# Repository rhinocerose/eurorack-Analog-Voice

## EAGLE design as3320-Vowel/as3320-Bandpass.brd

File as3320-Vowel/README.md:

# 3320 BPF

In Design

CC-BY-NC-SA 4.0

Based on :

https://github.com/forestcaver/Analog-Voice/tree/master/AJH_as3320_LPF

By  Forest Caver

Formant Information :
http://www.u.arizona.edu/~ohalad/Phonetics/notes/Formants%20Spectrograms%20and%20Vowels.PDF

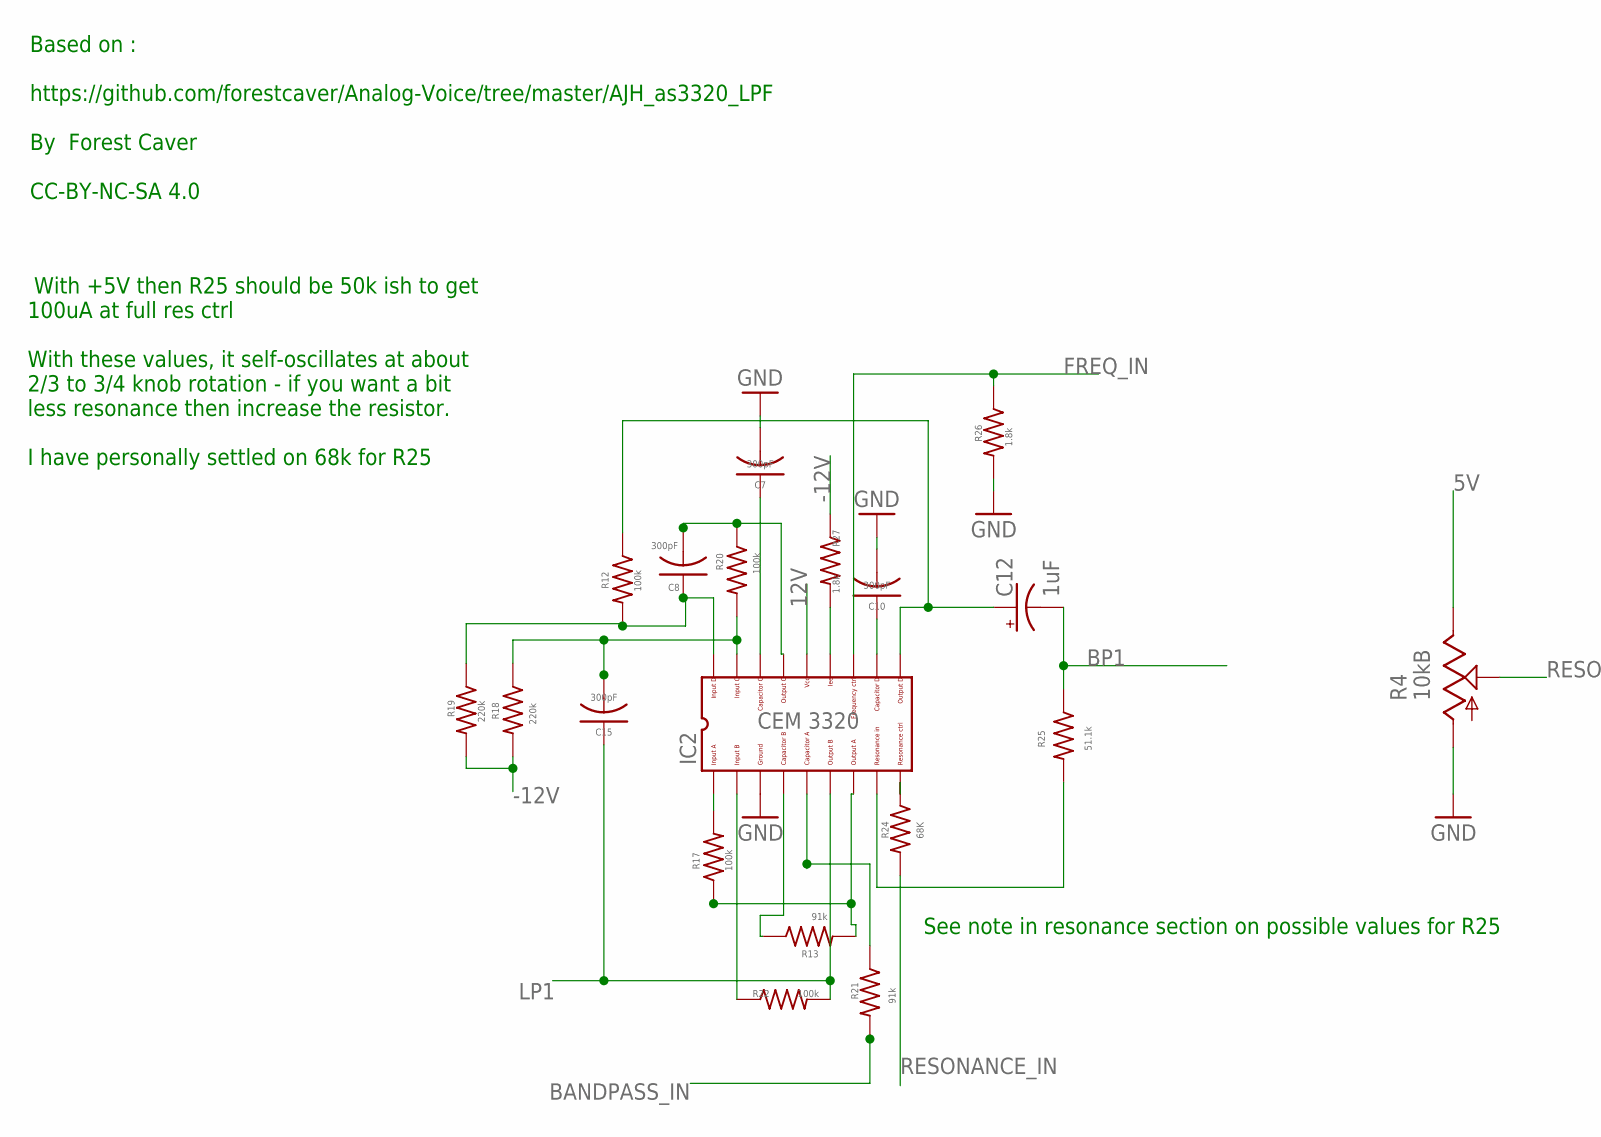
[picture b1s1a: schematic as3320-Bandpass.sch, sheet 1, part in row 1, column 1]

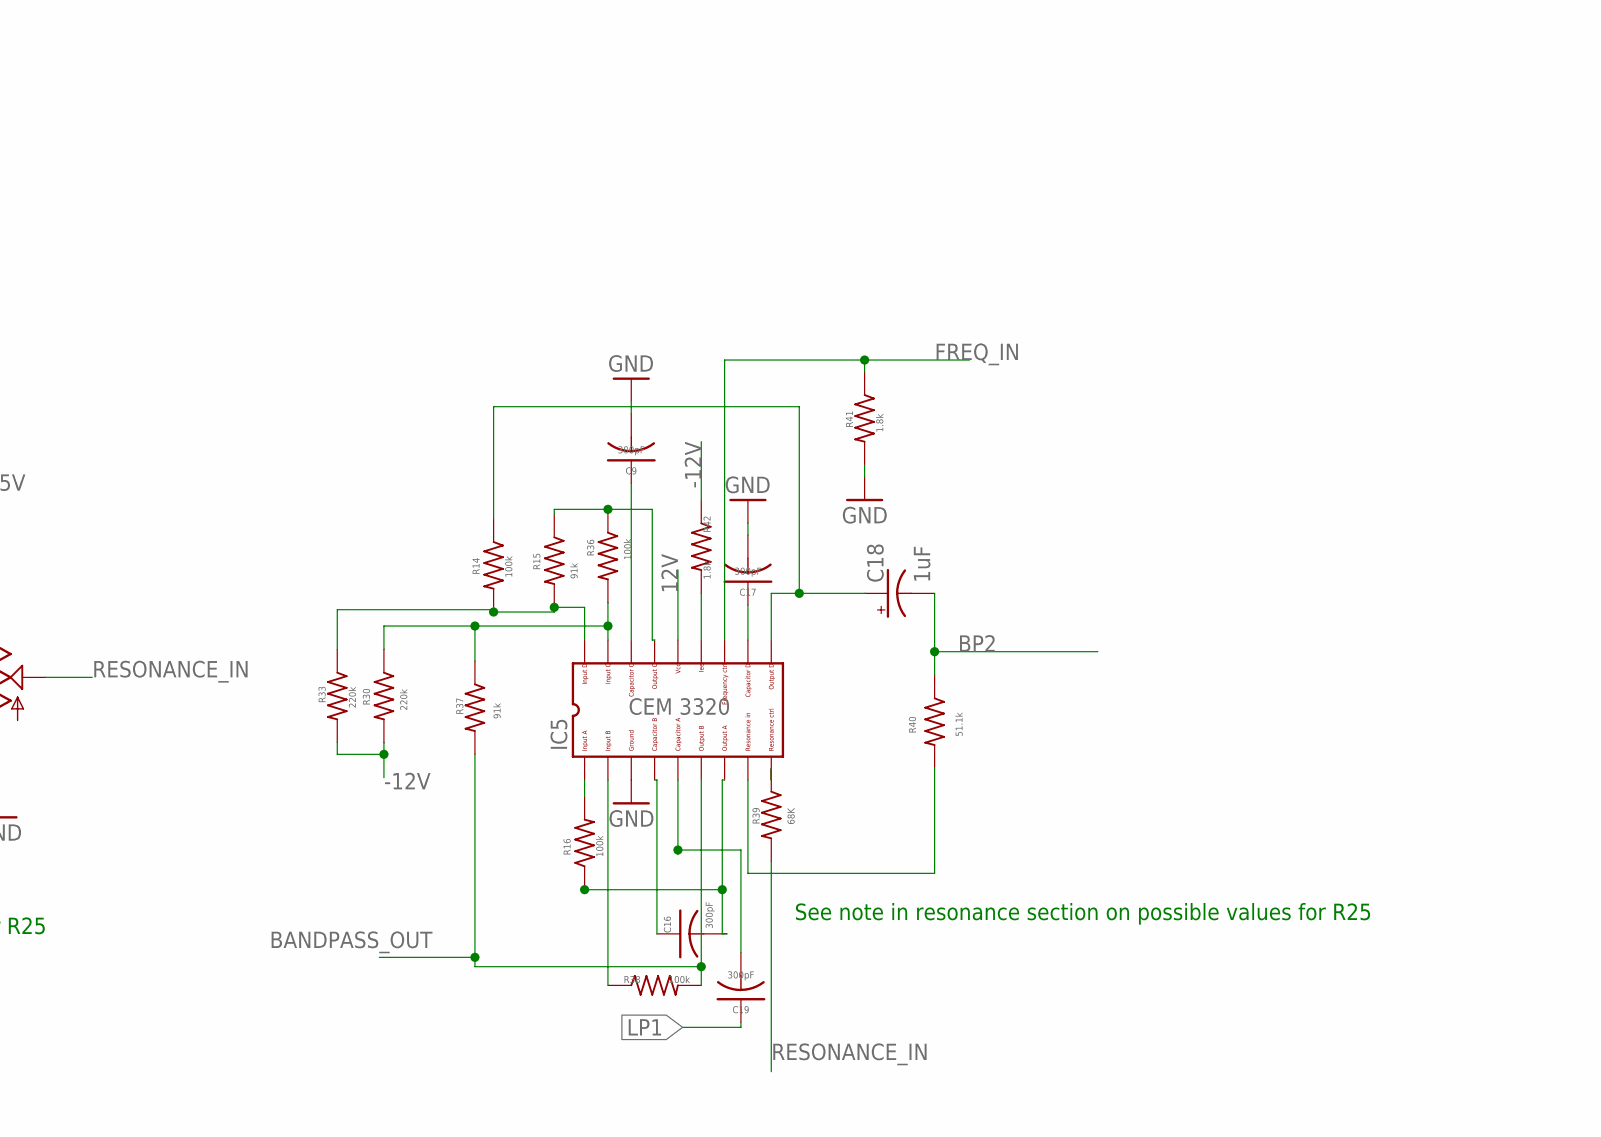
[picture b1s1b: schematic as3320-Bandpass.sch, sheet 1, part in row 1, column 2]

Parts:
C7, C8, C9, C10, C15, C16, C17, C19: 300pF; C0603
C12, C18: 1uF; PANASONIC_B
IC2, IC5: CEM3320; DIL18
R4: 10kB; ALPS_POT_VERTICAL
R12, R14, R16, R17, R20, R22, R36, R38: 100k; R0603
R13, R15, R21, R37: 91k; R0603
R18, R19, R30, R33: 220k; R0603
R24, R39: 68K; R0603
R25, R40: 51.1k; R0603
R26, R27, R41, R42: 1.8k; R0603

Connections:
5V: R4.P$1 (E); also elsewhere on the board
12V: IC2.14, IC5.14; also elsewhere on the board
-12V: R18.2, R19.2, R27.1, R30.2, R33.2, R42.1; also elsewhere on the board
BANDPASS_IN: R21.2; also elsewhere on the board
BANDPASS_OUT: IC5.6, R37.2, R38.2; also elsewhere on the board
BP1: C12.-, R25.1
BP2: C18.-, R40.1
FREQ_IN: IC2.12, IC5.12, R26.1, R41.1; also elsewhere on the board
GND: C7.2, C9.2, C10.2, C17.2, IC2.3, IC5.3, R4.P$3 (A), R26.2, R41.2; also elsewhere on the board
LP1: C15.1, C19.1, IC2.6, R22.2
unnamed: C10.1, IC2.11
unnamed: IC2.9, R24.1
unnamed: IC2.8, R25.2
unnamed: IC2.13, R27.2
unnamed: C17.1, IC5.11
unnamed: C7.1, IC2.16
unnamed: IC5.9, R39.1
unnamed: C12.+, IC2.10, R12.1
unnamed: IC2.5, R21.1
unnamed: IC2.7, R13.2, R17.1
unnamed: IC2.4, R13.1
unnamed: IC2.2, R22.1
unnamed: IC5.8, R40.2
unnamed: IC5.13, R42.2
unnamed: C9.1, IC5.16
unnamed: C18.+, IC5.10, R14.1
unnamed: C19.2, IC5.5
unnamed: C16.2, IC5.7, R16.1
unnamed: C16.1, IC5.4
unnamed: IC5.2, R38.1
unnamed: IC5.1, R16.2
unnamed: IC5.17, R30.1, R36.2, R37.1
unnamed: IC5.15, R15.1, R36.1
unnamed: IC5.18, R14.2, R15.2, R33.1
unnamed: IC2.1, R17.2
unnamed: C15.2, IC2.17, R18.1, R20.2
unnamed: C8.2, IC2.15, R20.1
unnamed: C8.1, IC2.18, R12.2, R19.1
RESONANCE_IN: R4.P$2 (S), R24.2, R39.2

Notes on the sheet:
With +5V then R25 should be 50k ish to get 100uA at full res ctrl With these values, it self-oscillates at about 2/3 to 3/4 knob rotation - if you want a bit less resonance then increase the resistor. I have personally settled on 68k for R25
Based on : https://github.com/forestcaver/Analog-Voice/tree/master/AJH_as3320_LPF By Forest Caver CC-BY-NC-SA 4.0
See note in resonance section on possible values for R25

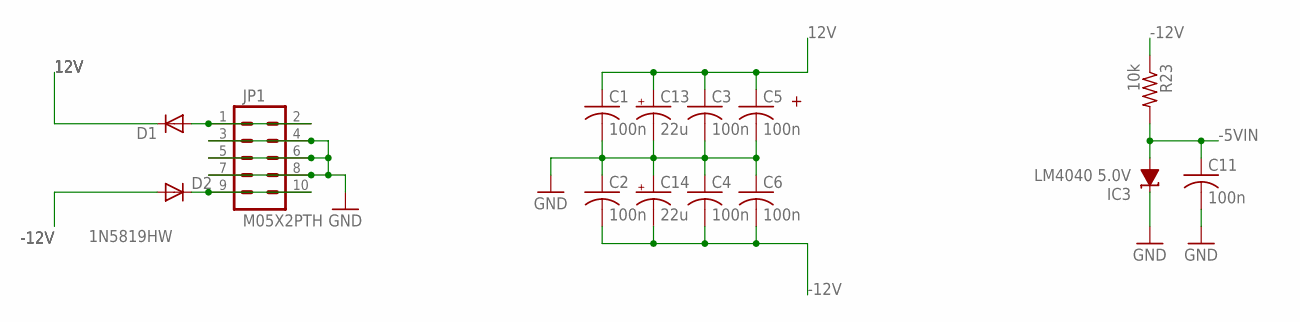
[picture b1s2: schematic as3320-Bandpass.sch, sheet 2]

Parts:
C1, C2, C3, C4, C5, C6, C11: 100n; C0603
C13, C14: 22u; PANASONIC_B
D1, D2: 1N5819HW; SOD123
IC3: LM4040 5.0V; DBZ_R-PDSO-G3
JP1: M05X2PTH; AVR_ICSP
R23: 10k; R0603

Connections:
12V: C1.1, C3.1, C5.1, C13.+, D1.C; also elsewhere on the board
-5VIN: C11.1, IC3.2 (A), R23.2; also elsewhere on the board
-12V: C2.2, C4.2, C6.2, C14.-, D2.A, R23.1; also elsewhere on the board
GND: C1.2, C2.1, C3.2, C4.1, C5.2, C6.1, C11.2, C13.-, C14.+, IC3.1 (C), JP1.3, JP1.4, JP1.5, JP1.6, JP1.7, JP1.8; also elsewhere on the board
unnamed: D1.A, JP1.1, JP1.2
unnamed: D2.C, JP1.9, JP1.10

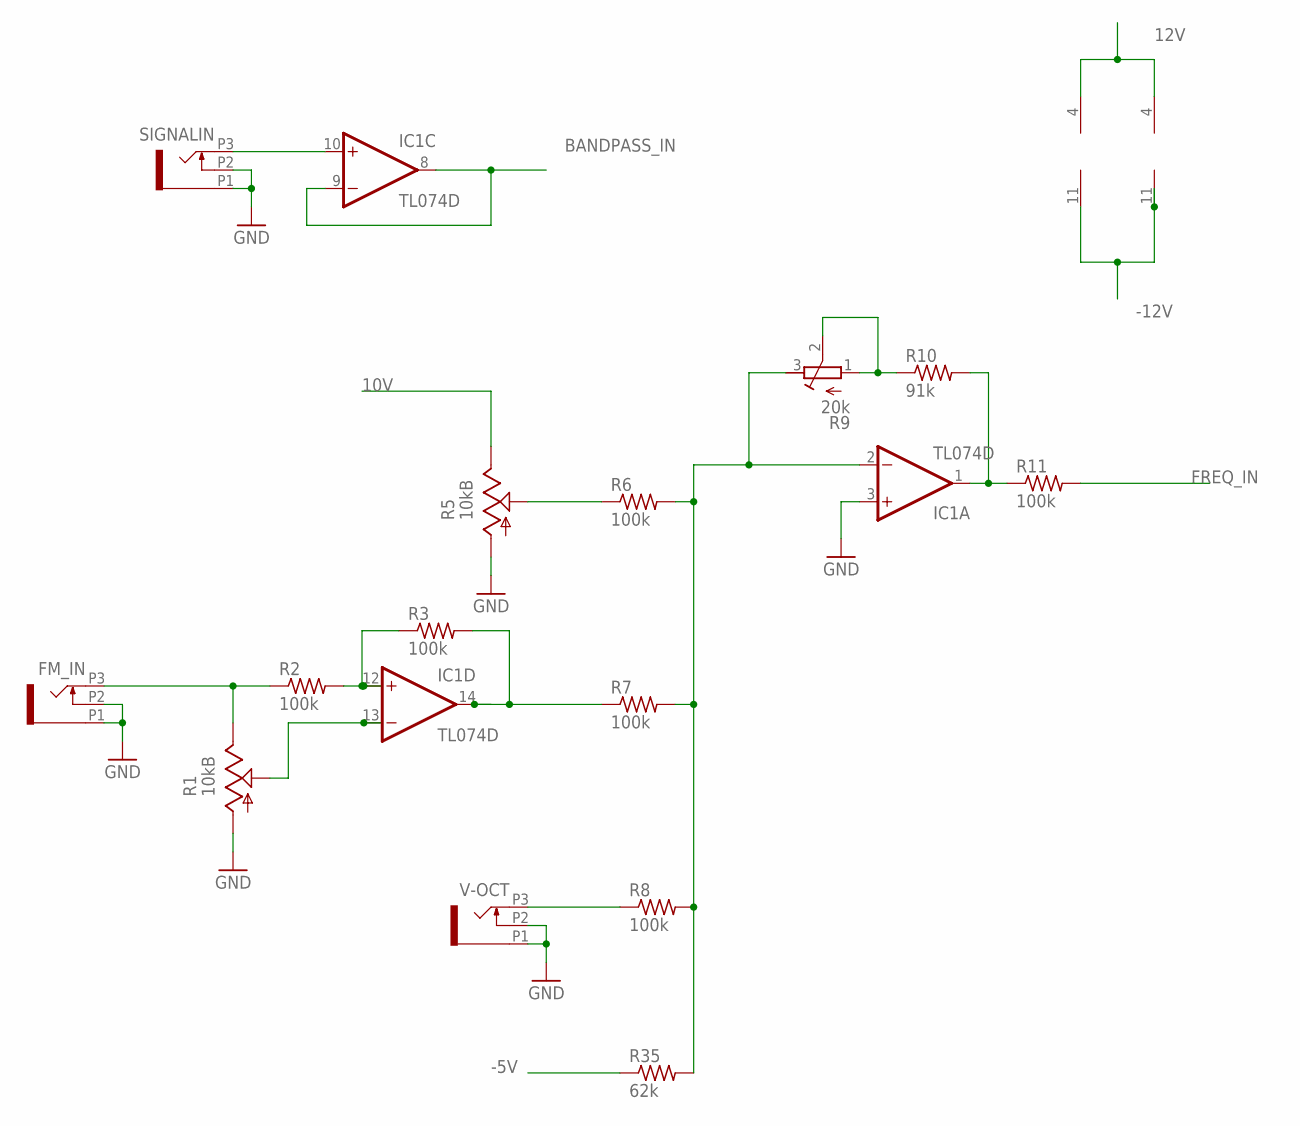
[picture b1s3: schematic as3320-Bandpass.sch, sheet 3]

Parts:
FM_IN: PJ301_THONKICONN6; WQP_PJ_301M6
IC1, IC4: TL074D; SO14
R1, R5: 10kB; ALPS_POT_VERTICAL
R2, R3, R6, R7, R8, R11: 100k; R0603
R9: 20k; RTRIM3296X
R10: 91k; R0603
R35: 62k; R0603
SIGNALIN: PJ301_THONKICONN6; WQP_PJ_301M6
V-OCT: PJ301_THONKICONN6; WQP_PJ_301M6

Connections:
10V: R5.P$1 (E); also elsewhere on the board
12V: IC1.4 (V+), IC4.4 (V+); also elsewhere on the board
-5V: R35.1; also elsewhere on the board
-12V: IC1.11 (V-), IC4.11 (V-); also elsewhere on the board
BANDPASS_IN: IC1.8 (OUT), IC1.9 (-IN); also elsewhere on the board
FREQ_IN: R11.2; also elsewhere on the board
GND: FM_IN.P1 (1), FM_IN.P2 (2), IC1.3 (+IN), R1.P$3 (A), R5.P$3 (A), SIGNALIN.P1 (1), SIGNALIN.P2 (2), V-OCT.P1 (1), V-OCT.P2 (2); also elsewhere on the board
unnamed: IC1.13 (-IN), R1.P$2 (S)
unnamed: R5.P$2 (S), R6.1
unnamed: IC1.12 (+IN), R2.2, R3.1
unnamed: IC1.2 (-IN), R6.2, R7.2, R8.2, R9.3 (A), R35.2
unnamed: IC1.1 (OUT), R10.2, R11.1
unnamed: IC1.10 (+IN), SIGNALIN.P3 (3)
unnamed: R8.1, V-OCT.P3 (3)
unnamed: IC1.14 (OUT), R3.2, R7.1
unnamed: R9.1 (E), R9.2 (S), R10.1
unnamed: FM_IN.P3 (3), R1.P$1 (E), R2.1

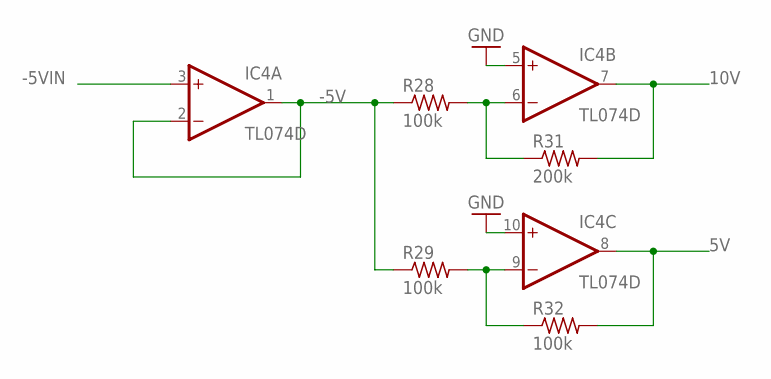
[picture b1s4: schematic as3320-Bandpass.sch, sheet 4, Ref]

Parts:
IC4: TL074D; SO14
R28, R29, R32: 100k; R0603
R31: 200k; R0603

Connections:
5V: IC4.8 (OUT), R32.2; also elsewhere on the board
10V: IC4.7 (OUT), R31.2; also elsewhere on the board
-5V: IC4.1 (OUT), IC4.2 (-IN), R28.1, R29.1; also elsewhere on the board
-5VIN: IC4.3 (+IN); also elsewhere on the board
GND: IC4.5 (+IN), IC4.10 (+IN); also elsewhere on the board
unnamed: IC4.9 (-IN), R29.2, R32.1
unnamed: IC4.6 (-IN), R28.2, R31.1

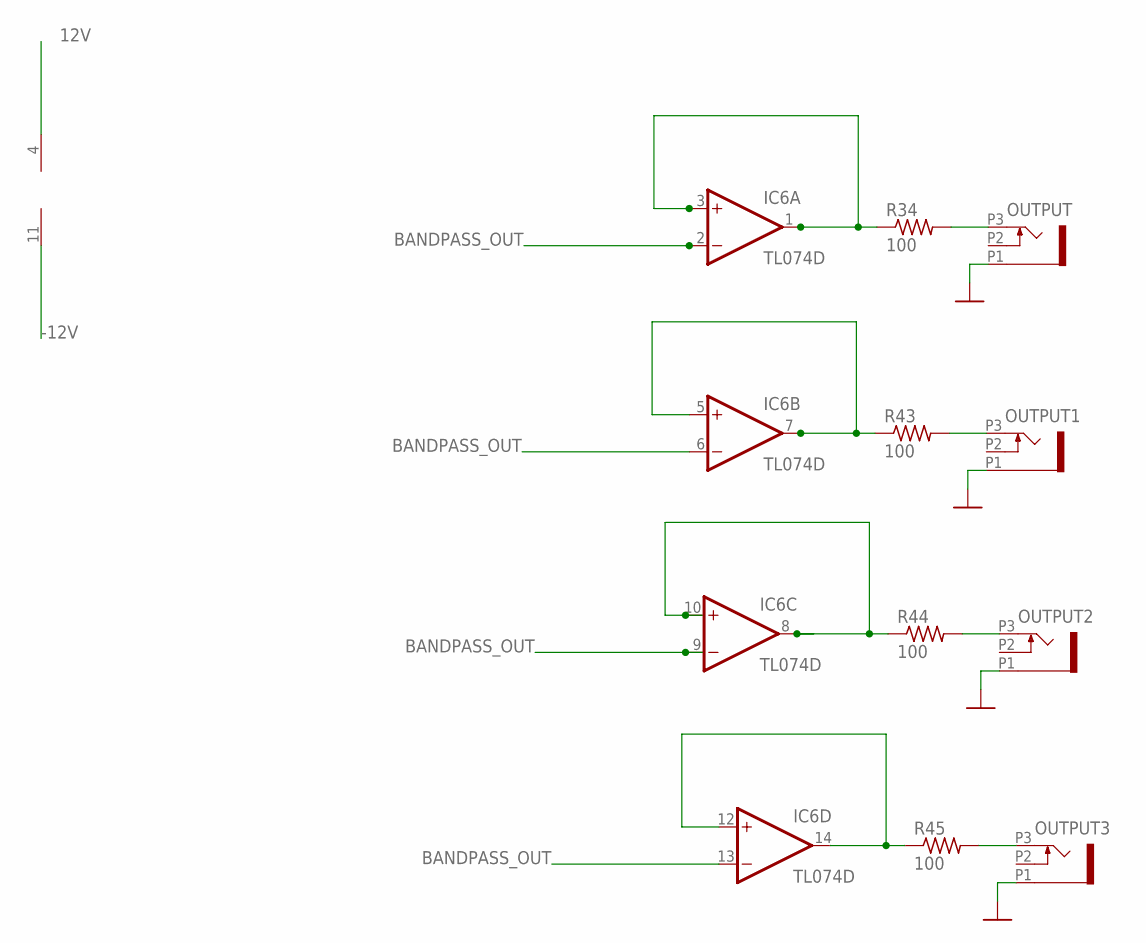
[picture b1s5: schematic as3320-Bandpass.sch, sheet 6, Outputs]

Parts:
IC6: TL074D; SO14
OUTPUT, OUTPUT1, OUTPUT2, OUTPUT3: PJ301_THONKICONN6; WQP_PJ_301M6
R34, R43, R44, R45: 100; R0603

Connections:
12V: IC6.4 (V+); also elsewhere on the board
-12V: IC6.11 (V-); also elsewhere on the board
BANDPASS_OUT: IC6.2 (-IN), IC6.6 (-IN), IC6.9 (-IN), IC6.13 (-IN); also elsewhere on the board
GND: OUTPUT.P1 (1), OUTPUT1.P1 (1), OUTPUT2.P1 (1), OUTPUT3.P1 (1); also elsewhere on the board
unnamed: IC6.1 (OUT), IC6.3 (+IN), R34.1
unnamed: OUTPUT.P3 (3), R34.2
unnamed: IC6.5 (+IN), IC6.7 (OUT), R43.1
unnamed: OUTPUT1.P3 (3), R43.2
unnamed: IC6.8 (OUT), IC6.10 (+IN), R44.1
unnamed: OUTPUT2.P3 (3), R44.2
unnamed: IC6.12 (+IN), IC6.14 (OUT), R45.1
unnamed: OUTPUT3.P3 (3), R45.2

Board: 2 copper layers, 80 parts (7 on the bottom side), 64 nets, no tracks yet.

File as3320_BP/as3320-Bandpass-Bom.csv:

"Library","Qty","Parts","Description","Value","Package","POPULARITY","SPICEPREFIX",
"og-pots","3","R1, R4, R5","","10kB","ALPS_POT_VERTICAL","","",
"og-pj301_variations","4","FM_IN, OUTPUT, SIGNALIN, V-OCT","","PJ301_THONKICONN6","WQP_PJ_301M6","","",
"rcl","7","C1, C2, C3, C4, C5, C6, C11","CAPACITOR, American symbol","100n","C0603","","",
"rcl","4","C7, C8, C10, C15","CAPACITOR, American symbol","300pF","C0603","37","C",
"CEM","1","IC2","CEM 3330 VCF","CEM3320","DIL18","","",
"diode","2","D1, D2","DIODE","1N5819HW","SOD123","","",
"og-header","1","JP1","Header 5x2","M05X2PTH","AVR_ICSP","","",
"linear","2","IC1, IC4","OP AMP","TL074D","SO14","0","",
"rcl","1","C12","POLARIZED CAPACITOR, American symbol","1uF","PANASONIC_B","0","C",
"rcl","2","C13, C14","POLARIZED CAPACITOR, American symbol","22u","PANASONIC_B","","",
"texas","1","IC3","PRECISION MICROPOWER SHUNT VOLTAGE REFERENCE","LM4040 5.0V","DBZ_R-PDSO-G3","","",
"rcl","2","R24, R26","RESISTOR, American symbol","1.8k","R0603","77","R",
"resistor","1","R34","RESISTOR, American symbol","100","R0603","","",
"resistor","9","R2, R3, R6, R7, R8, R11, R28, R29, R32","RESISTOR, American symbol","100k","R0603","","",
"rcl","4","R12, R18, R21, R22","RESISTOR, American symbol","100k","R0603","77","R",
"resistor","1","R23","RESISTOR, American symbol","10k","R0603","","",
"resistor","1","R31","RESISTOR, American symbol","200k","R0603","","",
"rcl","2","R13, R17","RESISTOR, American symbol","220k","R0603","77","R",
"rcl","1","R27","RESISTOR, American symbol","51.1k","R0603","77","R",
"resistor","1","R35","RESISTOR, American symbol","62k","R0603","","",
"rcl","1","R25","RESISTOR, American symbol","68K","R0603","77","R",
"resistor","1","R10","RESISTOR, American symbol","91k","R0603","","",
"rcl","2","R19, R20","RESISTOR, American symbol","91k","R0603","77","R",
"rcl","1","R9","Trimm resistor","20k","RTRIM3296X","","",

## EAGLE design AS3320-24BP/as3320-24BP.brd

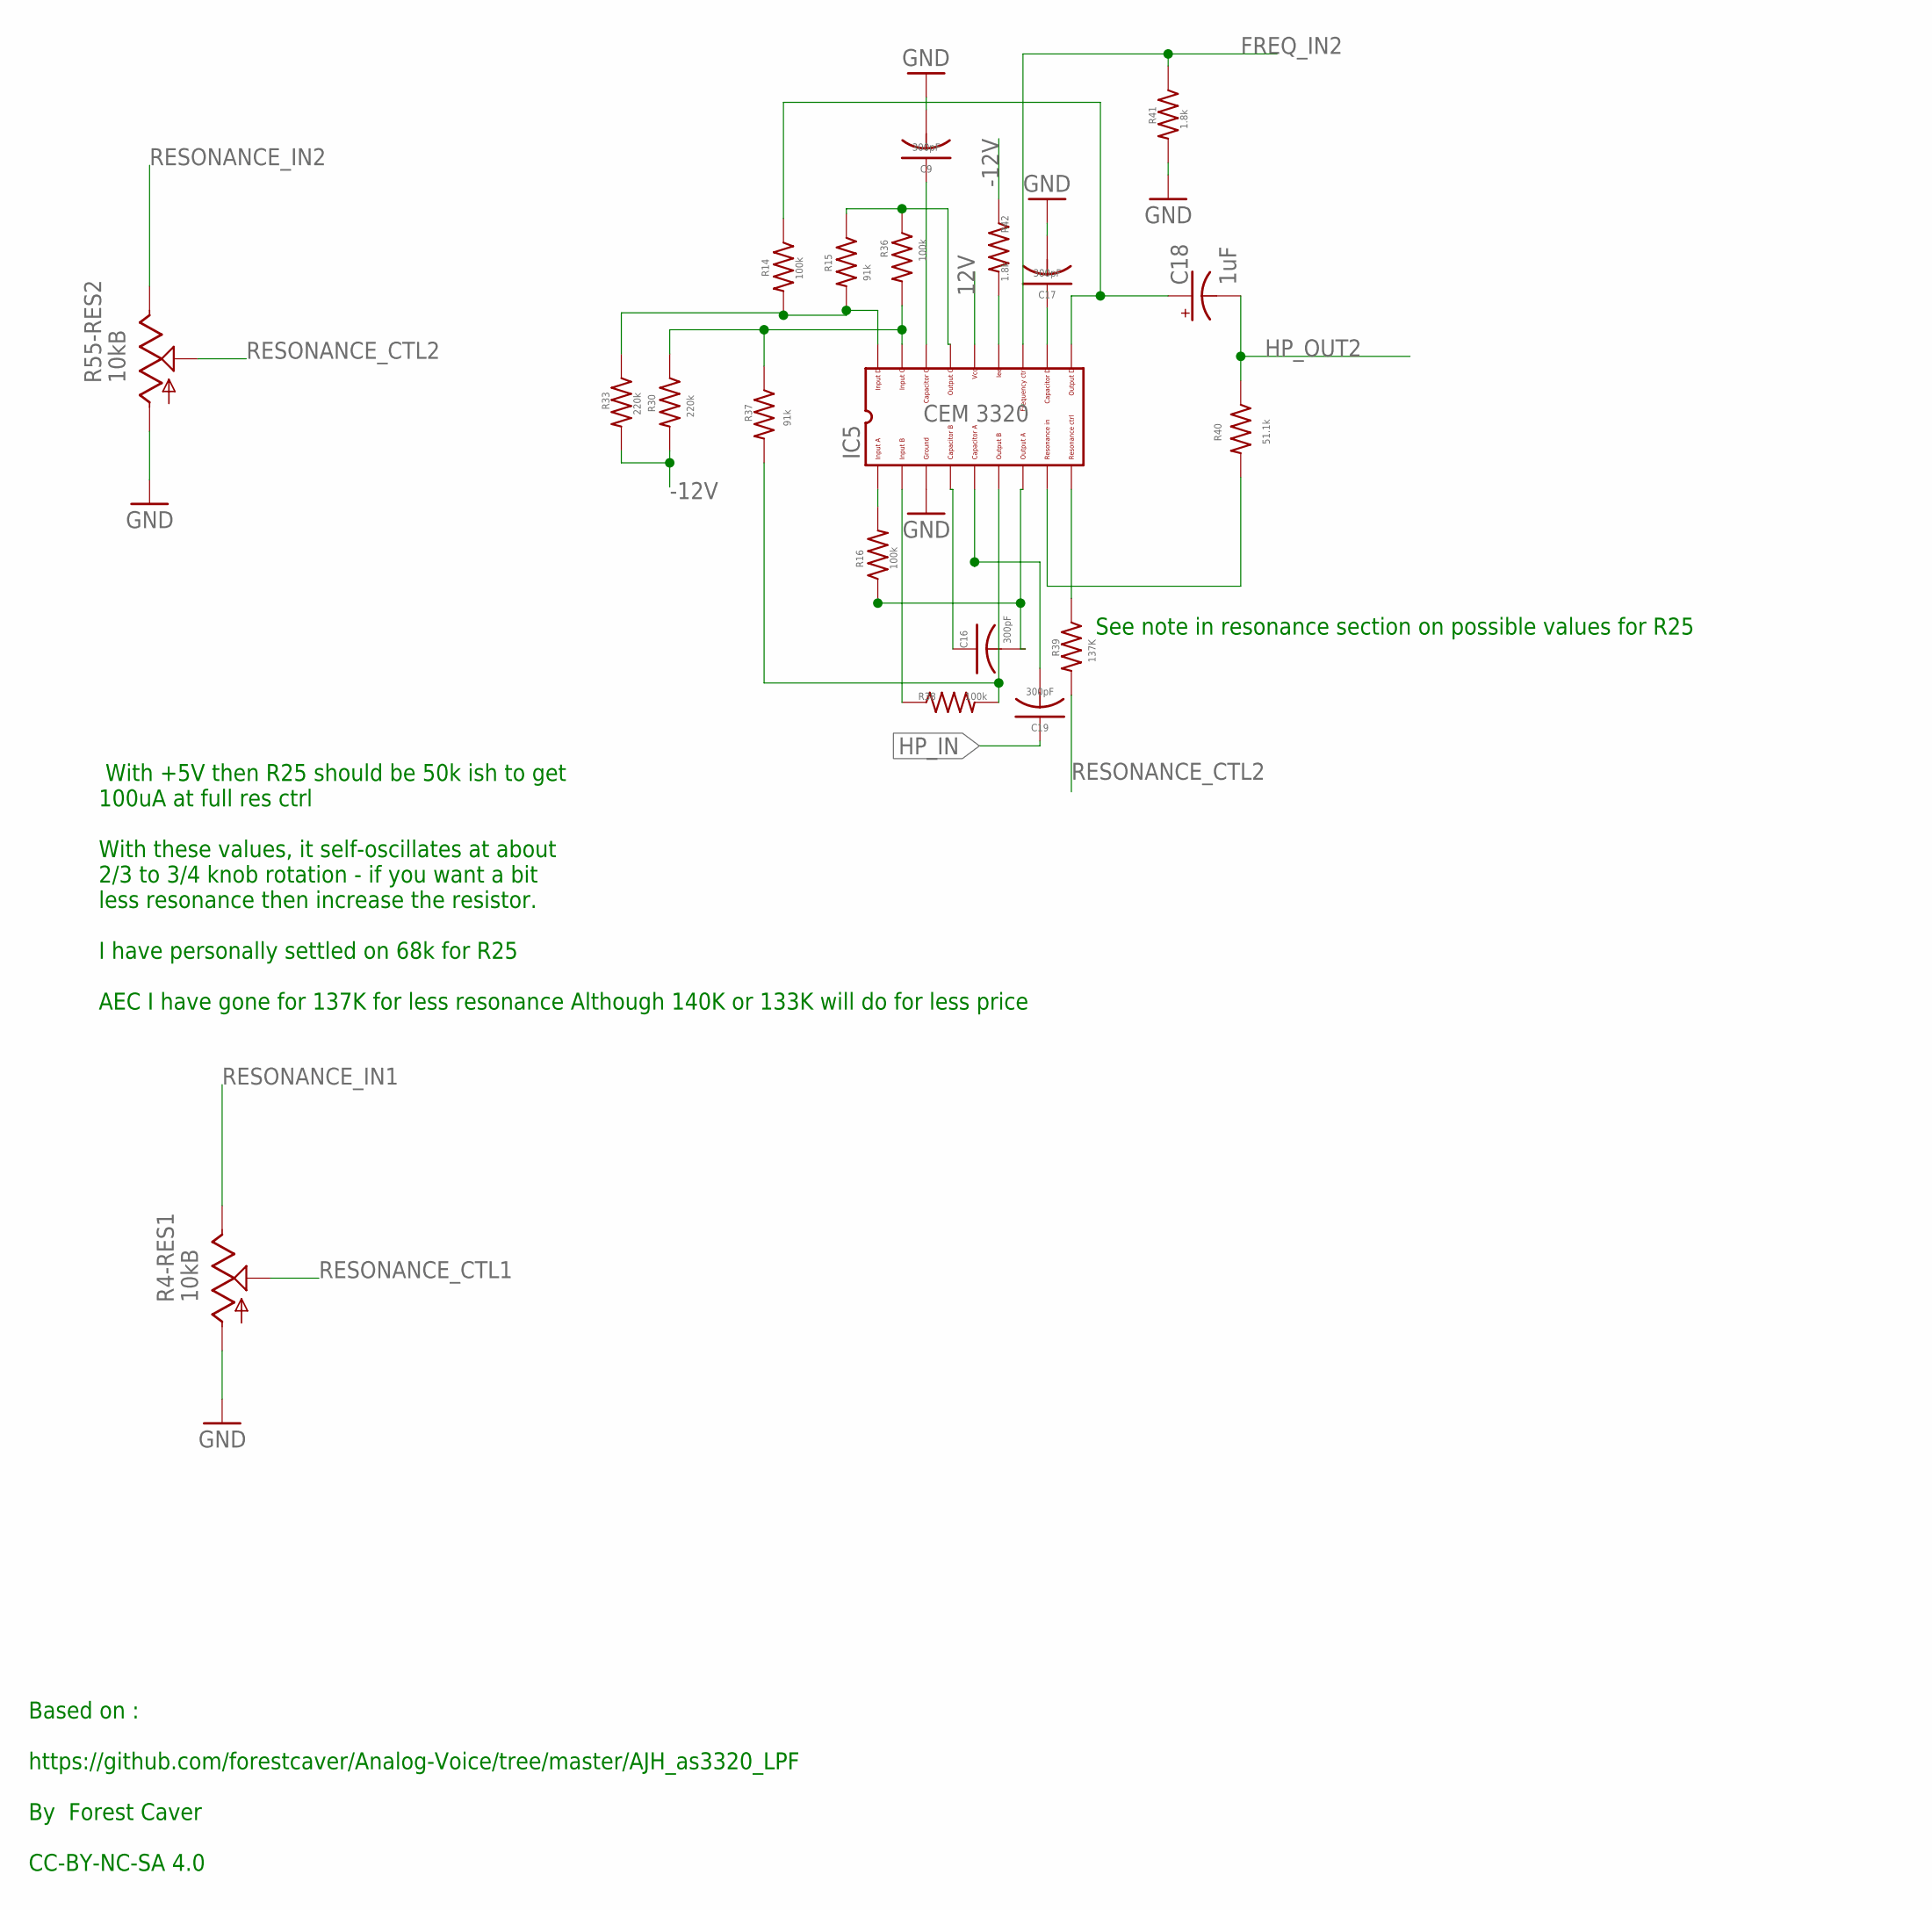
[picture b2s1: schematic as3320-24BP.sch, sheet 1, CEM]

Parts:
C9, C16, C17, C19: 300pF; C0805K
C18: 1uF; PANASONIC_B
IC5: CEM3320; DIL18
R4-RES1, R55-RES2: 10kB; ALPS_POT_VERTICAL
R14, R16, R36, R38: 100k; GMSN_M0805
R15, R37: 91k; GMSN_M0805
R30, R33: 220k; GMSN_M0805
R39: 137K; GMSN_M0805
R40: 51.1k; GMSN_M0805
R41, R42: 1.8k; GMSN_M0805

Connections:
12V: IC5.14; also elsewhere on the board
-12V: R30.2, R33.2, R42.1; also elsewhere on the board
FREQ_IN2: IC5.12, R41.1; also elsewhere on the board
GND: C9.2, C17.2, IC5.3, R4-RES1.P$3 (A), R41.2, R55-RES2.P$3 (A); also elsewhere on the board
HP_IN: C19.1; also elsewhere on the board
HP_OUT2: C18.-, R40.1; also elsewhere on the board
unnamed: C17.1, IC5.11
unnamed: IC5.9, R39.1
unnamed: IC5.8, R40.2
unnamed: IC5.13, R42.2
unnamed: C9.1, IC5.16
unnamed: C18.+, IC5.10, R14.1
unnamed: C19.2, IC5.5
unnamed: C16.2, IC5.7, R16.1
unnamed: C16.1, IC5.4
unnamed: IC5.2, R38.1
unnamed: IC5.6, R37.2, R38.2
unnamed: IC5.1, R16.2
unnamed: IC5.17, R30.1, R36.2, R37.1
unnamed: IC5.15, R15.1, R36.1
unnamed: IC5.18, R14.2, R15.2, R33.1
RESONANCE_CTL1: R4-RES1.P$2 (S)
RESONANCE_CTL2: R39.2, R55-RES2.P$2 (S)
RESONANCE_IN1: R4-RES1.P$1 (E); also elsewhere on the board
RESONANCE_IN2: R55-RES2.P$1 (E); also elsewhere on the board

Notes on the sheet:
With +5V then R25 should be 50k ish to get 100uA at full res ctrl With these values, it self-oscillates at about 2/3 to 3/4 knob rotation - if you want a bit less resonance then increase the resistor. I have personally settled on 68k for R25 AEC I have gone for 137K for less resonance Although 140K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
Based on : https://github.com/forestcaver/Analog-Voice/tree/master/AJH_as3320_LPF By Forest Caver CC-BY-NC-SA 4.0
See note in resonance section on possible values for R25

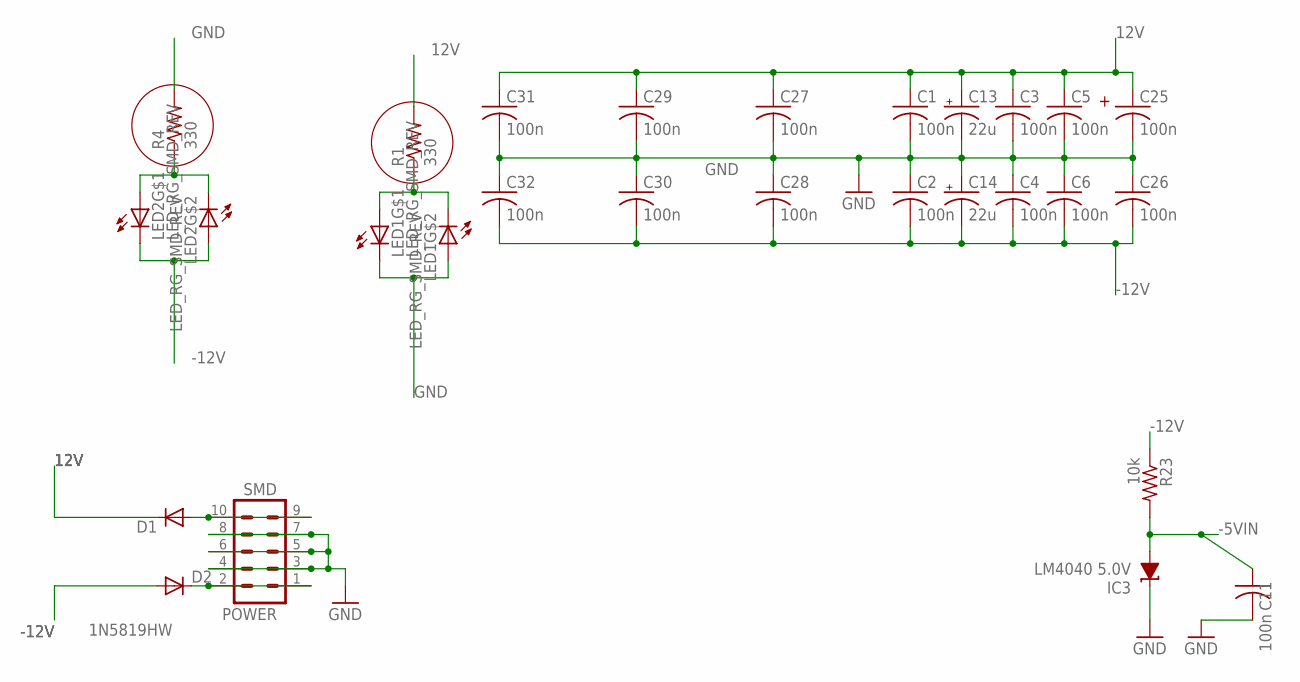
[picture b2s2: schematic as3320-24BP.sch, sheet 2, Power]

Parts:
C1, C2, C3, C4, C5, C6, C25, C26, C27, C28, C29, C30, C31, C32: 100n; C0805K
C11: 100n; GMSN_C0805K
C13, C14: 22u; PANASONIC_B
D1, D2: 1N5819HW; SOD123
IC3: LM4040 5.0V; DBZ_R-PDSO-G3
LED1, LED2: LED_RG_SMD_REV; LSG_T77K
POWER: SMD; 2X5-SHROUDED_SMD
R1, R4: 330; GMSN_M0805
R23: 10k; GMSN_M0805

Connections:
12V: C1.1, C3.1, C5.1, C13.+, C25.1, C27.1, C29.1, C31.1, D1.C, R1.2; also elsewhere on the board
-5VIN: C11.1, IC3.2 (A), R23.2; also elsewhere on the board
-12V: C2.2, C4.2, C6.2, C14.-, C26.2, C28.2, C30.2, C32.2, D2.A, LED2.1 (C), LED2.4 (A), R23.1; also elsewhere on the board
-12V-P: D2.C, POWER.1, POWER.2
GND: C1.2, C2.1, C3.2, C4.1, C5.2, C6.1, C11.2, C13.-, C14.+, C25.2, C26.1, C27.2, C28.1, C29.2, C30.1, C31.2, C32.1, IC3.1 (C), LED1.1 (C), LED1.4 (A), POWER.3, POWER.4, POWER.5, POWER.6, POWER.7, POWER.8, R4.2; also elsewhere on the board
unnamed: D1.A, POWER.9, POWER.10
unnamed: LED2.2 (A), LED2.3 (C), R4.1
unnamed: LED1.2 (A), LED1.3 (C), R1.1

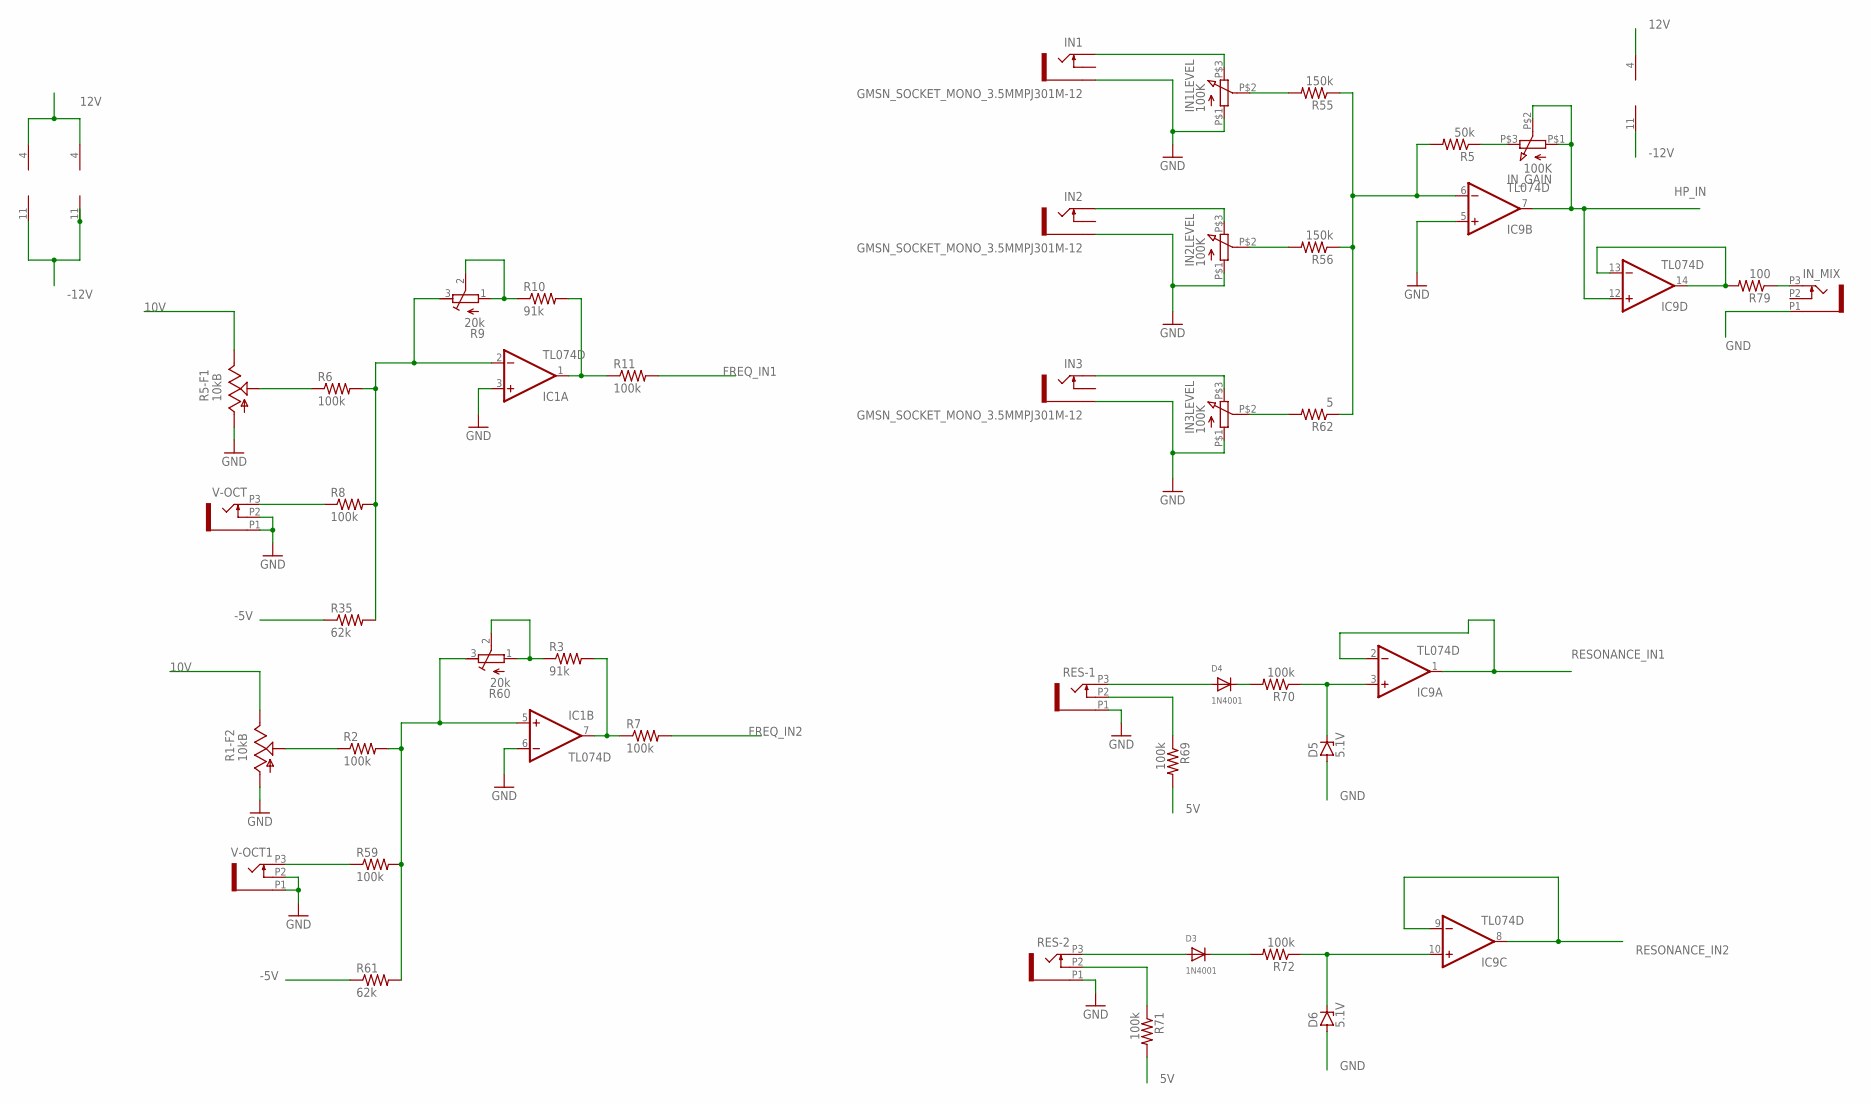
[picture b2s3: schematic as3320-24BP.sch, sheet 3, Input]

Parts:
D3, D4: 1N4001; SMADIODE
D5, D6: 5.1V; SOT23
IC1, IC4, IC9: TL074D; SO14
IN1, IN2, IN3: GMSN_SOCKET_MONO_3.5MMPJ301M-12; GMSN_PJ301M-12
IN1LEVEL, IN2LEVEL, IN3LEVEL: 100K; POT
IN_GAIN: 100K; POT
IN_MIX: PJ301_THONKICONN6; WQP_PJ_301M6
R1-F2, R5-F1: 10kB; ALPS_POT_VERTICAL
R2, R6, R7, R8, R11, R59, R70, R72: 100k; GMSN_M0805
R3, R10: 91k; GMSN_M0805
R5: 50k; GMSN_M0805
R9, R60: 20k; RTRIM3296X
R35, R61: 62k; GMSN_M0805
R55, R56: 150k; R0805
R62: 5; R0805
R69, R71: 100k; R0805
R79: 100; GMSN_M0805
RES-1, RES-2: PJ301_THONKICONN6; WQP_PJ_301M6
V-OCT, V-OCT1: PJ301_THONKICONN6; WQP_PJ_301M6

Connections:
5V: R69.2, R71.2; also elsewhere on the board
10V: R1-F2.P$1 (E), R5-F1.P$1 (E); also elsewhere on the board
12V: IC1.4 (V+), IC4.4 (V+), IC9.4 (V+); also elsewhere on the board
-5V: R35.1, R61.1; also elsewhere on the board
-12V: IC1.11 (V-), IC4.11 (V-), IC9.11 (V-); also elsewhere on the board
FREQ_IN1: R11.2
FREQ_IN2: R7.2; also elsewhere on the board
GND: D5.1 (A), D6.1 (A), IC1.3 (+IN), IC1.6 (-IN), IC9.5 (+IN), IN1.GND (SLEEVE), IN1LEVEL.P$1 (1), IN2.GND (SLEEVE), IN2LEVEL.P$1 (1), IN3.GND (SLEEVE), IN3LEVEL.P$1 (1), IN_MIX.P1 (1), R1-F2.P$3 (A), R5-F1.P$3 (A), RES-1.P1 (1), RES-2.P1 (1), V-OCT.P1 (1), V-OCT.P2 (2), V-OCT1.P1 (1), V-OCT1.P2 (2); also elsewhere on the board
HP_IN: IC9.7 (OUT), IC9.12 (+IN), IN_GAIN.P$1 (1), IN_GAIN.P$2 (2); also elsewhere on the board
unnamed: IC1.7 (OUT), R3.2, R7.1
unnamed: R5-F1.P$2 (S), R6.1
unnamed: R1-F2.P$2 (S), R2.1
unnamed: IC1.2 (-IN), R6.2, R8.2, R9.3 (A), R35.2
unnamed: IC1.1 (OUT), R10.2, R11.1
unnamed: R71.1, RES-2.P2 (2)
unnamed: R8.1, V-OCT.P3 (3)
unnamed: IC1.5 (+IN), R2.2, R59.2, R60.3 (A), R61.2
unnamed: IN_GAIN.P$3 (3), R5.1
unnamed: R9.1 (E), R9.2 (S), R10.1
unnamed: R59.1, V-OCT1.P3 (3)
unnamed: R3.1, R60.1 (E), R60.2 (S)
unnamed: IN1.TIP, IN1LEVEL.P$3 (3)
unnamed: IN2.TIP, IN2LEVEL.P$3 (3)
unnamed: D3.A, RES-2.P3 (3)
unnamed: IN1LEVEL.P$2 (2), R55.2
unnamed: IN2LEVEL.P$2 (2), R56.2
unnamed: R69.1, RES-1.P2 (2)
unnamed: IN3.TIP, IN3LEVEL.P$3 (3)
unnamed: IN3LEVEL.P$2 (2), R62.2
unnamed: IC9.6 (-IN), R5.2, R55.1, R56.1, R62.1
unnamed: D3.C, R72.2
unnamed: D4.A, RES-1.P3 (3)
unnamed: D4.C, R70.2
unnamed: D5.3 (C), IC9.3 (+IN), R70.1
unnamed: D6.3 (C), IC9.10 (+IN), R72.1
unnamed: IC9.13 (-IN), IC9.14 (OUT), R79.2
unnamed: IN_MIX.P3 (3), R79.1
RESONANCE_IN1: IC9.1 (OUT), IC9.2 (-IN); also elsewhere on the board
RESONANCE_IN2: IC9.8 (OUT), IC9.9 (-IN); also elsewhere on the board

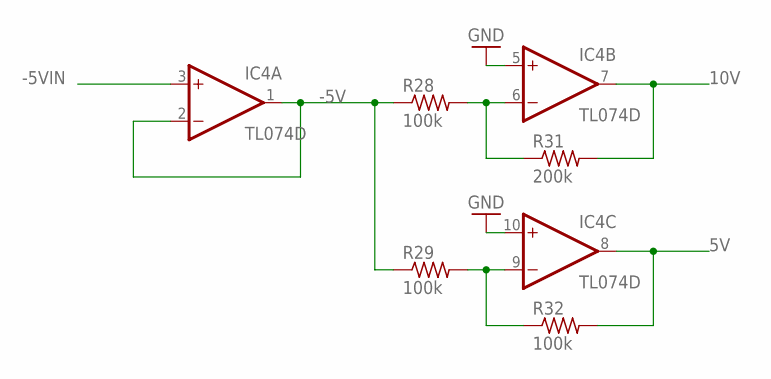
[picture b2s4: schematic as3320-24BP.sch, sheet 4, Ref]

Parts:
IC4: TL074D; SO14
R28, R29, R32: 100k; GMSN_M0805
R31: 200k; GMSN_M0805

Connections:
5V: IC4.8 (OUT), R32.2; also elsewhere on the board
10V: IC4.7 (OUT), R31.2; also elsewhere on the board
-5V: IC4.1 (OUT), IC4.2 (-IN), R28.1, R29.1; also elsewhere on the board
-5VIN: IC4.3 (+IN); also elsewhere on the board
GND: IC4.5 (+IN), IC4.10 (+IN); also elsewhere on the board
unnamed: IC4.9 (-IN), R29.2, R32.1
unnamed: IC4.6 (-IN), R28.2, R31.1

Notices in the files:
AS3320-24BP/as3320-24BP.brd:
CC BY 3.0
parts and their libraries:
SparkFun-Connectors: Licensing: Creative Commons ShareAlike 4.0 International - https://creativecommons.org/licenses/by-sa/4.0
